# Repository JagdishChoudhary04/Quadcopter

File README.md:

# Quadcopter

Welcome to my Quadcopter Build Project! This repository documents the journey of creating a fully functional quadcopter from the ground up. This project encompasses the design and development of both a custom remote controller and a flight controller, showcasing the integration of hardware and software to achieve seamless flight operations.

## Overview
In this project, I aimed to explore the principles of quadcopter design, including aerodynamics, electronics, and programming. By building the quadcopter from scratch, I gained hands-on experience with various components and technologies, from selecting the right motors and propellers to coding the flight control algorithms.
## Key Features
* Custom Quadcopter Frame: Designed and 3D printed a lightweight yet durable frame tailored for stability and agility.

* Remote Controller: Developed a user-friendly remote controller, featuring an intuitive interface for precise control.

* Flight Controller: Programmed a flight controller with advanced stabilization algorithms, enabling smooth and responsive flight.

* Telemetry Integration: Incorporated real-time telemetry for monitoring performance and flight data.

* Modular Design: Ensured easy access to components for maintenance and upgrades.
## Contribution
Feel free to contribute by reporting issues, suggesting features, or sharing your own modifications. Collaboration is welcome!
##  About Me
I'm a Third Year Student Pursuing Bachleors of Engineering 
in Electronics and Telecommunication. For any queries : jagdishchoudhary9372@gmail.com
## Index
 * Introduction
 * What will you Learn?
 * Getting Started & Software Requirement
 * Making our own Flight Controller
 * Conclusion

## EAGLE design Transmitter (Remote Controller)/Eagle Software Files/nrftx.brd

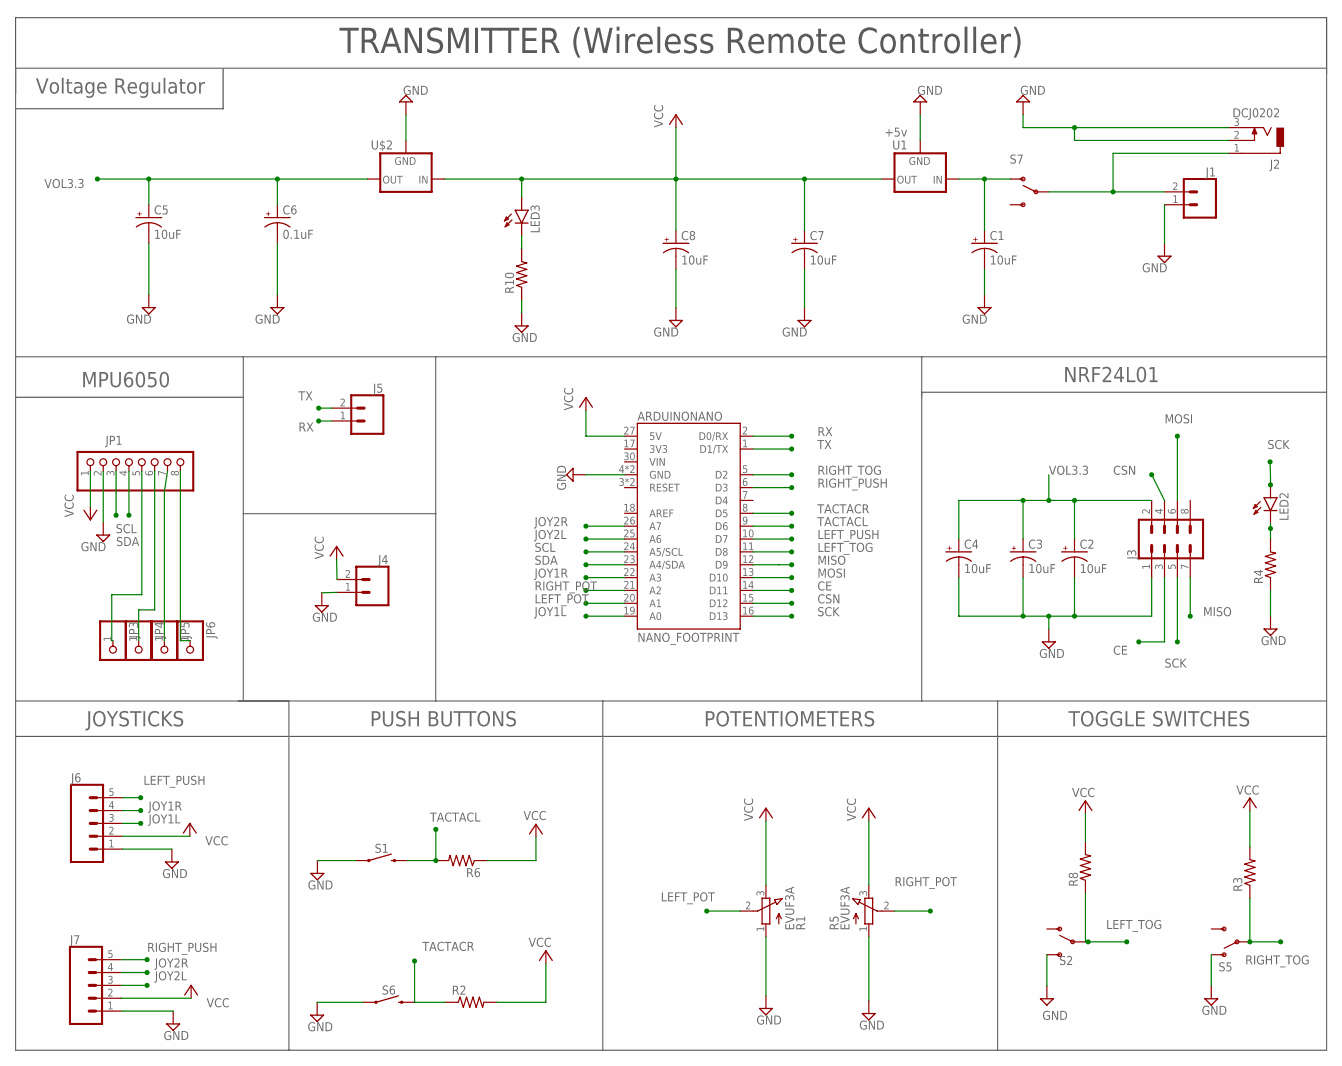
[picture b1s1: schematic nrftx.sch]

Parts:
ARDUINONANO: NANO_FOOTPRINT; NANO
C1, C2, C3, C4, C5, C7, C8: 10uF; CPOL-RADIAL-2.5MM-5MM-KIT
C6: 0.1uF; CPOL-RADIAL-2.5MM-5MM-KIT
J1, J4, J5: CONN_02; 1X02
J2: DCJ0202
J3: CONN_04X2; 2X4
J6, J7: CONN_05PTH; 1X05
JP1: PINHD-1X8; 1X08
JP3, JP4, JP5, JP6: PINHD-1X1; 1X01
LED2, LED3: LED5MM
R1, R5: EVUF3A; EVUF
R2, R3, R4, R6, R8, R10: R-US_M1206; M1206
S1, S6: MOMENTARY-SWITCH-SPST-PTH-6.0MM-KIT; TACTILE_SWITCH_PTH_6.0MM_KIT
S2, S5, S7: SWITCH-SPDT-PTH-11.6X4.0MM-KIT; SWITCH_SPDT_PTH_11.6X4.0MM_KIT
U1: +5v; TO-252
U$2: V_REG_LD1117VXX; TO-220-ALT2

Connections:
CE: ARDUINONANO.14 (D11), J3.3
CSN: ARDUINONANO.15 (D12), J3.4
GND: ARDUINONANO.4 (GND), ARDUINONANO.29 (GND), C1.2 (-), C2.2 (-), C3.2 (-), C4.2 (-), C5.2 (-), C6.2 (-), C7.2 (-), C8.2 (-), J1.1, J2.2, J2.3, J3.1, J4.1, J6.1, J7.1, JP1.2, R1.1 (A), R4.1, R5.1 (A), R10.1, S1.1, S2.3 (S), S5.1 (O), S6.1, U1.3 (GND), U$2.GND
JOY1L: ARDUINONANO.19 (A0), J6.3
JOY1R: ARDUINONANO.22 (A3), J6.4
JOY2L: ARDUINONANO.25 (A6), J7.3
JOY2R: ARDUINONANO.26 (A7), J7.4
LEFT_POT: ARDUINONANO.20 (A1), R1.2 (S)
LEFT_PUSH: ARDUINONANO.10 (D7), J6.5
LEFT_TOG: ARDUINONANO.11 (D8), R8.1, S2.2
MISO: ARDUINONANO.12 (D9), J3.7
MOSI: ARDUINONANO.13 (D10), J3.6
unnamed: LED2.K (C), R4.2
unnamed: JP1.5, JP3.1
unnamed: JP1.6, JP4.1
unnamed: JP1.7, JP5.1
unnamed: JP1.8, JP6.1
unnamed: C1.1 (+), S7.1 (O), U1.1 (IN)
unnamed: LED3.K (C), R10.2
unnamed: J1.2, J2.1, S7.2
RIGHT_POT: ARDUINONANO.21 (A2), R5.2 (S)
RIGHT_PUSH: ARDUINONANO.6 (D3), J7.5
RIGHT_TOG: ARDUINONANO.5 (D2), R3.1, S5.2
RX: ARDUINONANO.2 (D0/RX), J5.1
SCK: ARDUINONANO.16 (D13), J3.5, LED2.A
SCL: ARDUINONANO.24 (A5/SCL), JP1.3
SDA: ARDUINONANO.23 (A4/SDA), JP1.4
TACTACL: ARDUINONANO.9 (D6), R6.2, S1.3 (2)
TACTACR: ARDUINONANO.8 (D5), R2.1, S6.3 (2)
TX: ARDUINONANO.1 (D1/TX), J5.2
VCC: ARDUINONANO.27 (5V), C7.1 (+), C8.1 (+), J4.2, J6.2, J7.2, JP1.1, LED3.A, R1.3 (E), R2.2, R3.2, R5.3 (E), R6.1, R8.2, U1.2 (OUT), U$2.IN
VOL3.3: C2.1 (+), C3.1 (+), C4.1 (+), C5.1 (+), C6.1 (+), J3.2, U$2.OUT

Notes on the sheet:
TRANSMITTER (Wireless Remote Controller)
Voltage Regulator
MPU6050
NRF24L01
PUSH BUTTONS
JOYSTICKS
POTENTIOMETERS
TOGGLE SWITCHES

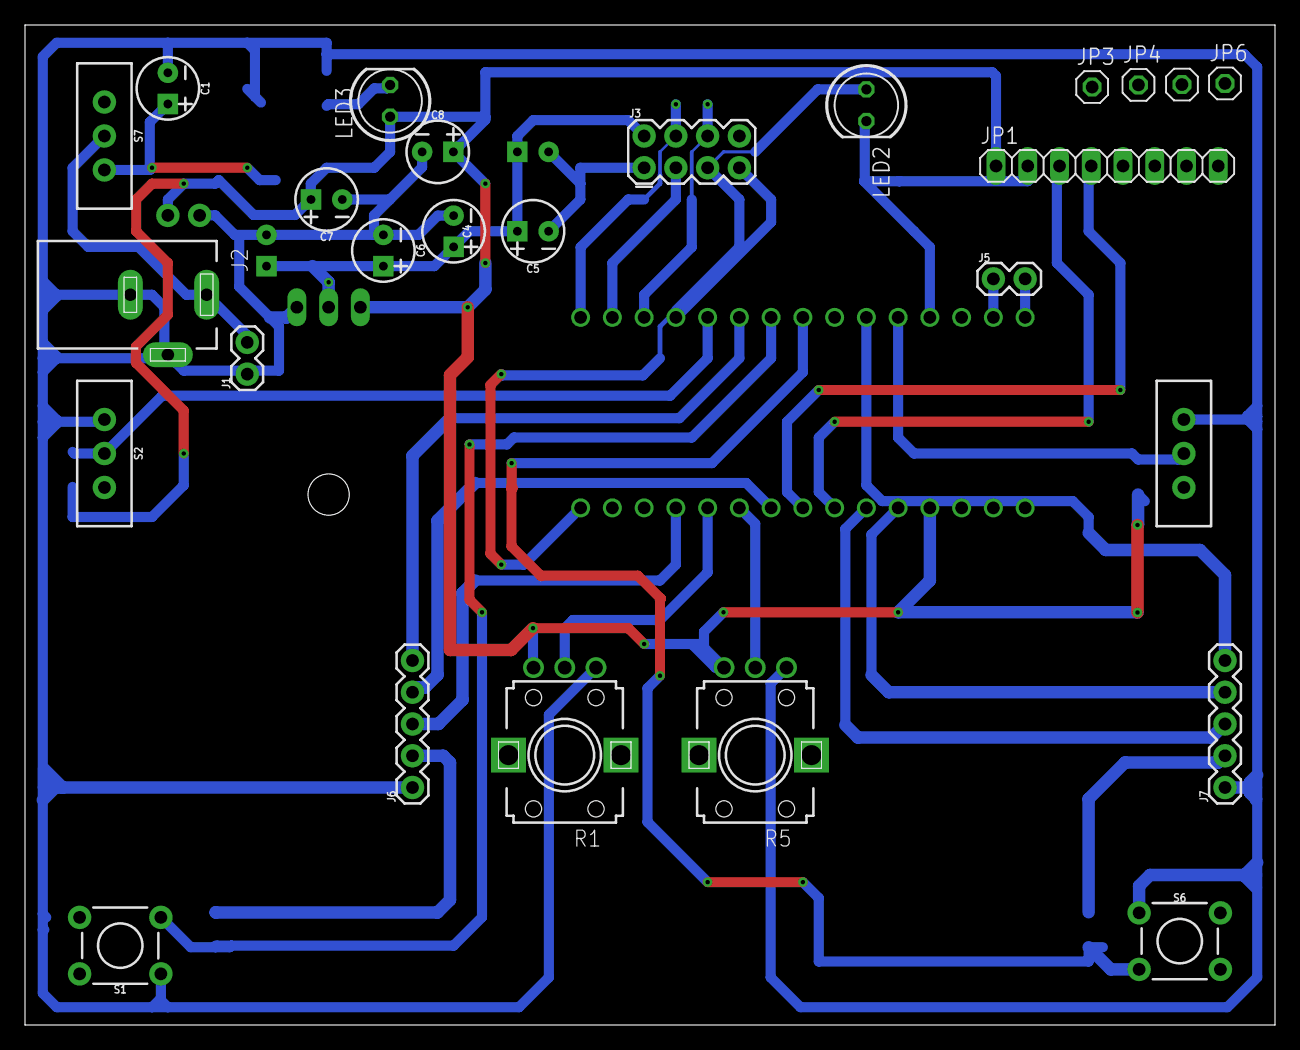
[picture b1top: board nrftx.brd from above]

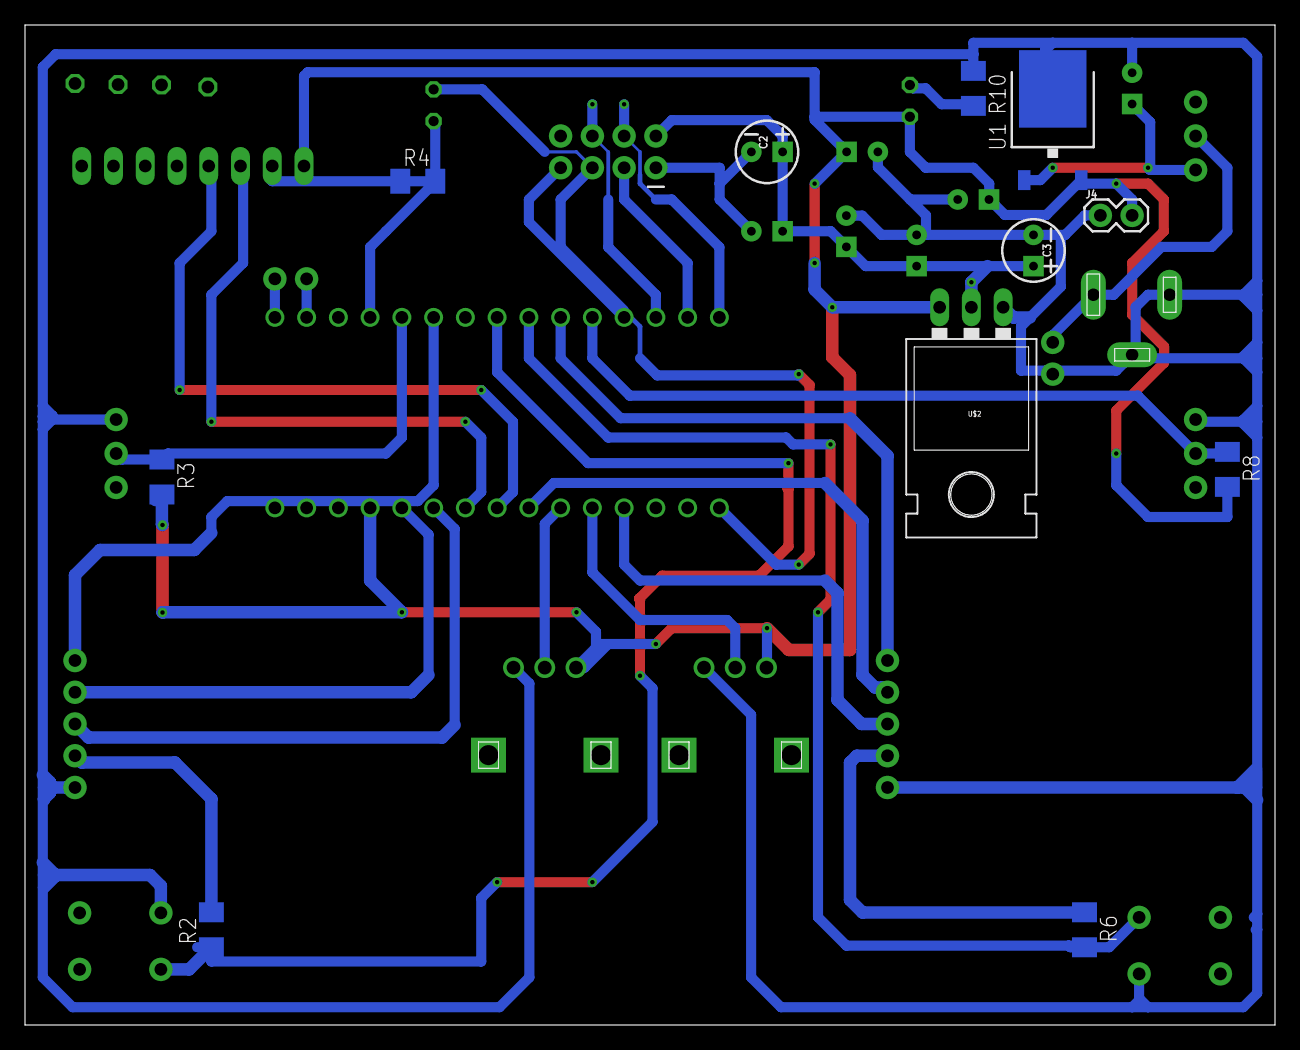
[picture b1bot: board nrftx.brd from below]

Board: 2 copper layers, 100.0 x 80.0 mm, 38 parts (11 on the bottom side), 32 nets.

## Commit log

2024-09-24 Quadcopter
2024-10-02 Updated Design
2024-10-02 Updated PCB Design
2024-10-02 Readme File
2025-08-03 Added Design files

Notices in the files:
parts and their libraries:
SparkFun-Boards: Licensing: Creative Commons ShareAlike 4.0 International - https://creativecommons.org/licenses/by-sa/4.0
